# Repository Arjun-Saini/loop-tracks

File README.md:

# loop-tracks

This is the main repository for the loop-tracks project.
The server and UI for this project can be found at [loop-tracks-server](https://github.com/cogsandsquigs/loop-tracks-server) and [loop-tracks-ui](https://github.com/cogsandsquigs/loop-tracks-ui). Full documentation and other information for the project located [here](https://arjun-saini.notion.site/arjun-saini/Loop-Tracks-0d7150e50bd84f2c9db64b674ca986d8).

## images and diagrams

Images and diagrams used in the notion page.

## PCB Design

PCB project files for each track component, designed with [KiCad 6](https://www.kicad.org/).

## master

Master I2C device, code written for a [Particle Argon](https://docs.particle.io/argon/) using DeviceOS 5.0.0.

## slave

Slave I2C devices, code written for an [ATmega328p](https://www.microchip.com/en-us/product/ATmega328).

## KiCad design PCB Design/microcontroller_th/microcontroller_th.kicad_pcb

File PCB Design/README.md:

# loop-tracks PCB designs
These are the PCB designs for the loop-tracks project

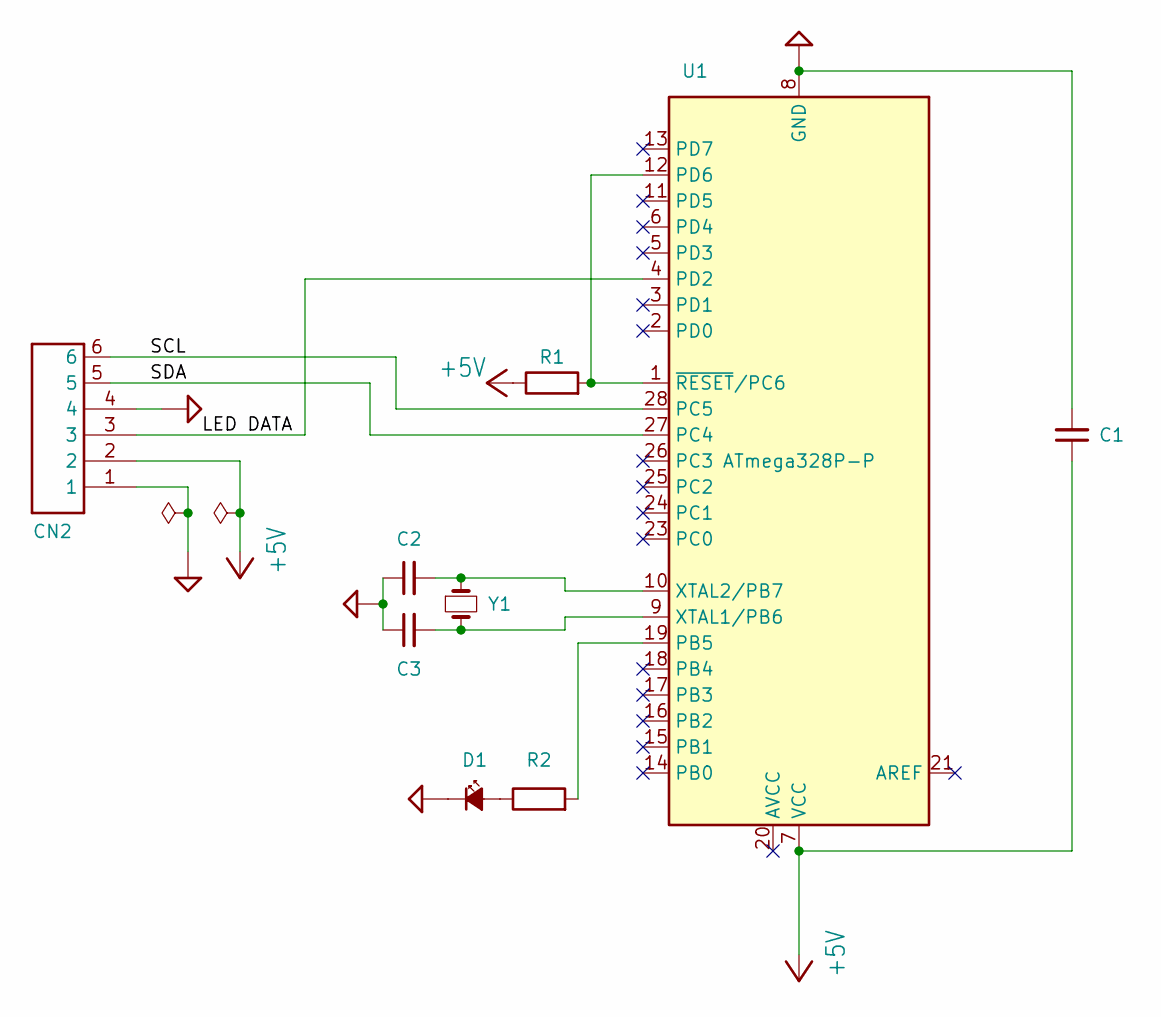
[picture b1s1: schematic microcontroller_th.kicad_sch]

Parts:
C1, C2, C3: C_Small; C_Disc_D4.7mm_W2.5mm_P5.00mm
CN2: 1X4SMT; 1X4-SMT
D1: LED_Small_Filled; LED_D3.0mm
R1, R2: R; R_Axial_DIN0207_L6.3mm_D2.5mm_P7.62mm_Horizontal
U1: ATmega328P-P; DIP-28_W7.62mm
Y1: Crystal_Small; Crystal_HC49-U_Vertical

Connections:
+5V: C1.1, CN2.2, R1.1, U1.7 (VCC)
/LED DATA: CN2.3, U1.4 (PD2)
/SCL: CN2.6, U1.28 (PC5)
/SDA: CN2.5, U1.27 (PC4)
GND: C1.2, C2.1, C3.1, CN2.1, CN2.4, D1.1 (K), U1.8 (GND), U1.22 (GND)
unnamed: C2.2, U1.10 (XTAL2/PB7), Y1.1
unnamed: C3.2, U1.9 (XTAL1/PB6), Y1.2
unnamed: D1.2 (A), R2.1
unnamed: R2.2, U1.19 (PB5)
unnamed: R1.2, U1.1 (~RESET/PC6), U1.12 (PD6)

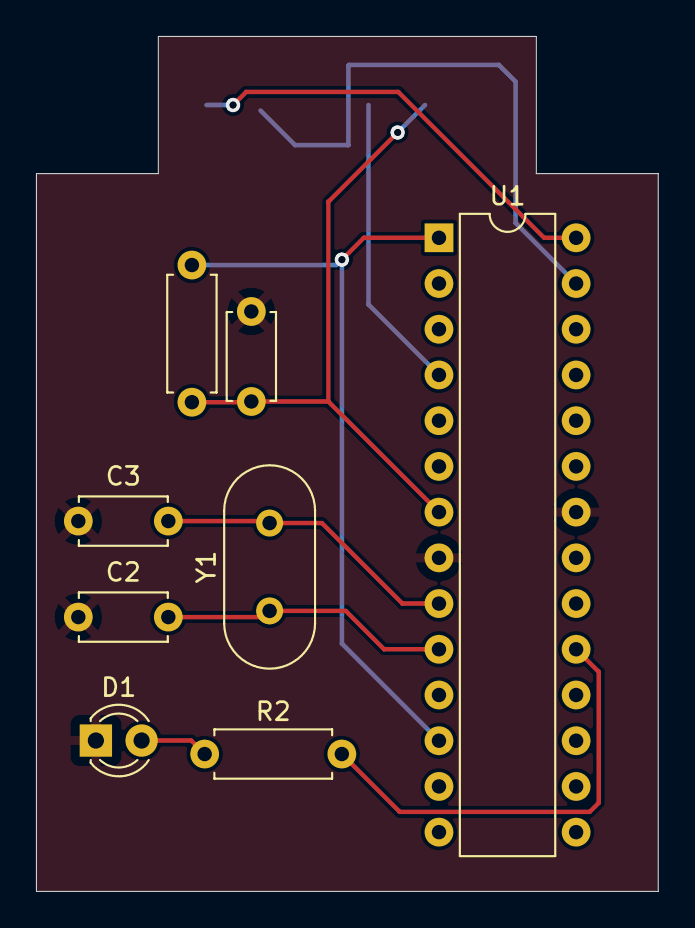
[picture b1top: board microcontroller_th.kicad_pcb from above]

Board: 2 copper layers, 34.5 x 47.5 mm, 9 parts (1 on the bottom side), 10 nets.

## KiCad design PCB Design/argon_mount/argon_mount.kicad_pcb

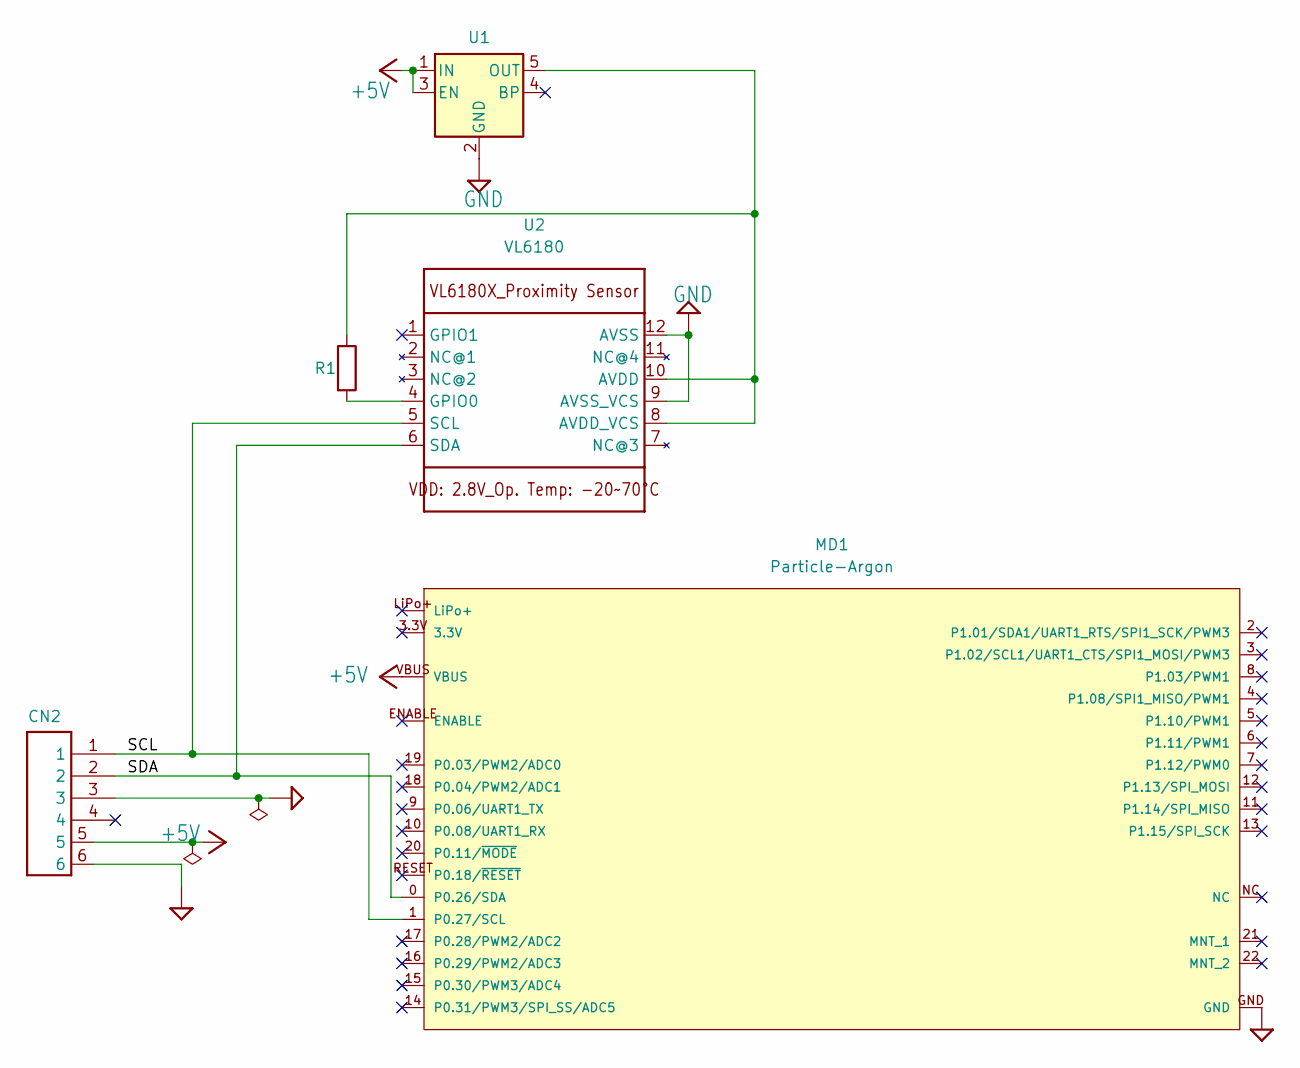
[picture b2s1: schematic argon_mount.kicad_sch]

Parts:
CN2: 1X4SMT; 1X4-SMT
MD1: Particle-Argon; Particle-Argon-0-0-MD1; manufacturer Particle; digikey description Bluetooth, WiFi 802.11b/g/n, Bluetooth 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
R1: R; R_Axial_DIN0207_L6.3mm_D2.5mm_P7.62mm_Horizontal
U1: MIC5219-2.85YM5; SOT-23-5
U2: VL6180

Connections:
+5V: CN2.5, MD1.VBUS, U1.1 (IN), U1.3 (EN)
/SCL: CN2.1, MD1.1 (P0.27/SCL), U2.5 (SCL)
/SDA: CN2.2, MD1.0 (P0.26/SDA), U2.6 (SDA)
GND: CN2.3, CN2.6, MD1.GND, U1.2 (GND), U2.9 (AVSS_VCS), U2.12 (AVSS)
unnamed: R1.1, U1.5 (OUT), U2.8 (AVDD_VCS), U2.10 (AVDD)
unnamed: R1.2, U2.4 (GPIO0)

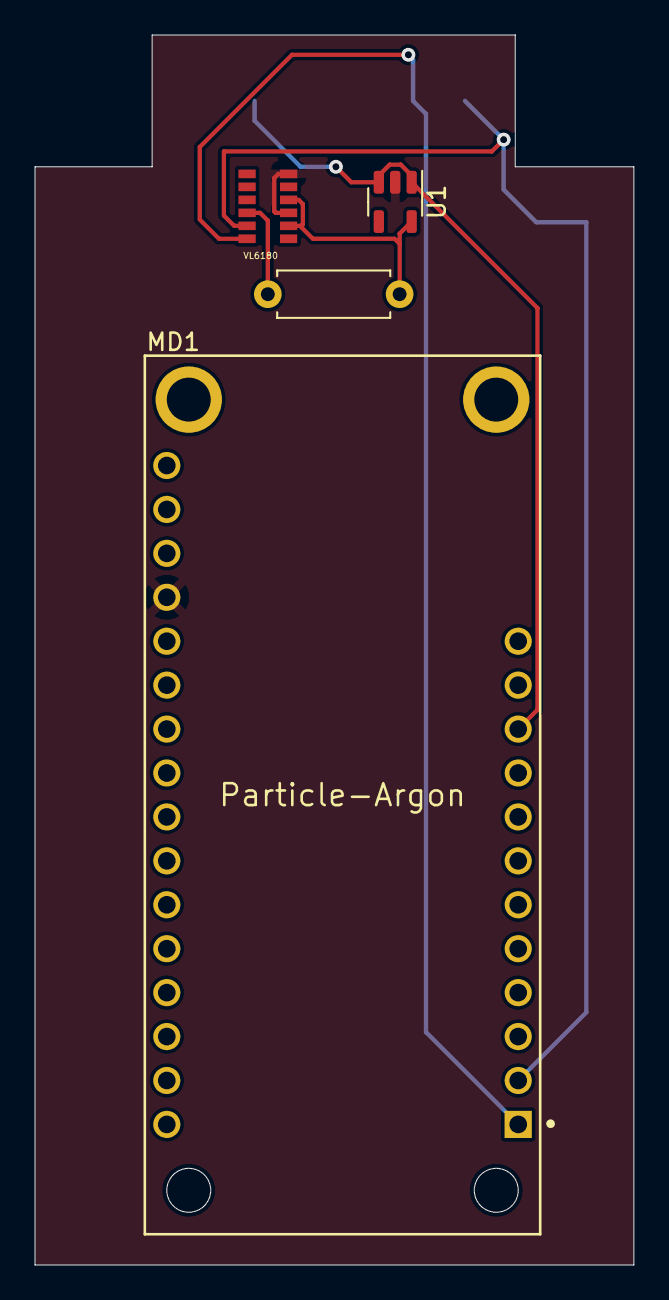
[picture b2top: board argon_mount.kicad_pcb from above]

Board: 2 copper layers, 34.6 x 71.1 mm, 5 parts (1 on the bottom side), 6 nets.

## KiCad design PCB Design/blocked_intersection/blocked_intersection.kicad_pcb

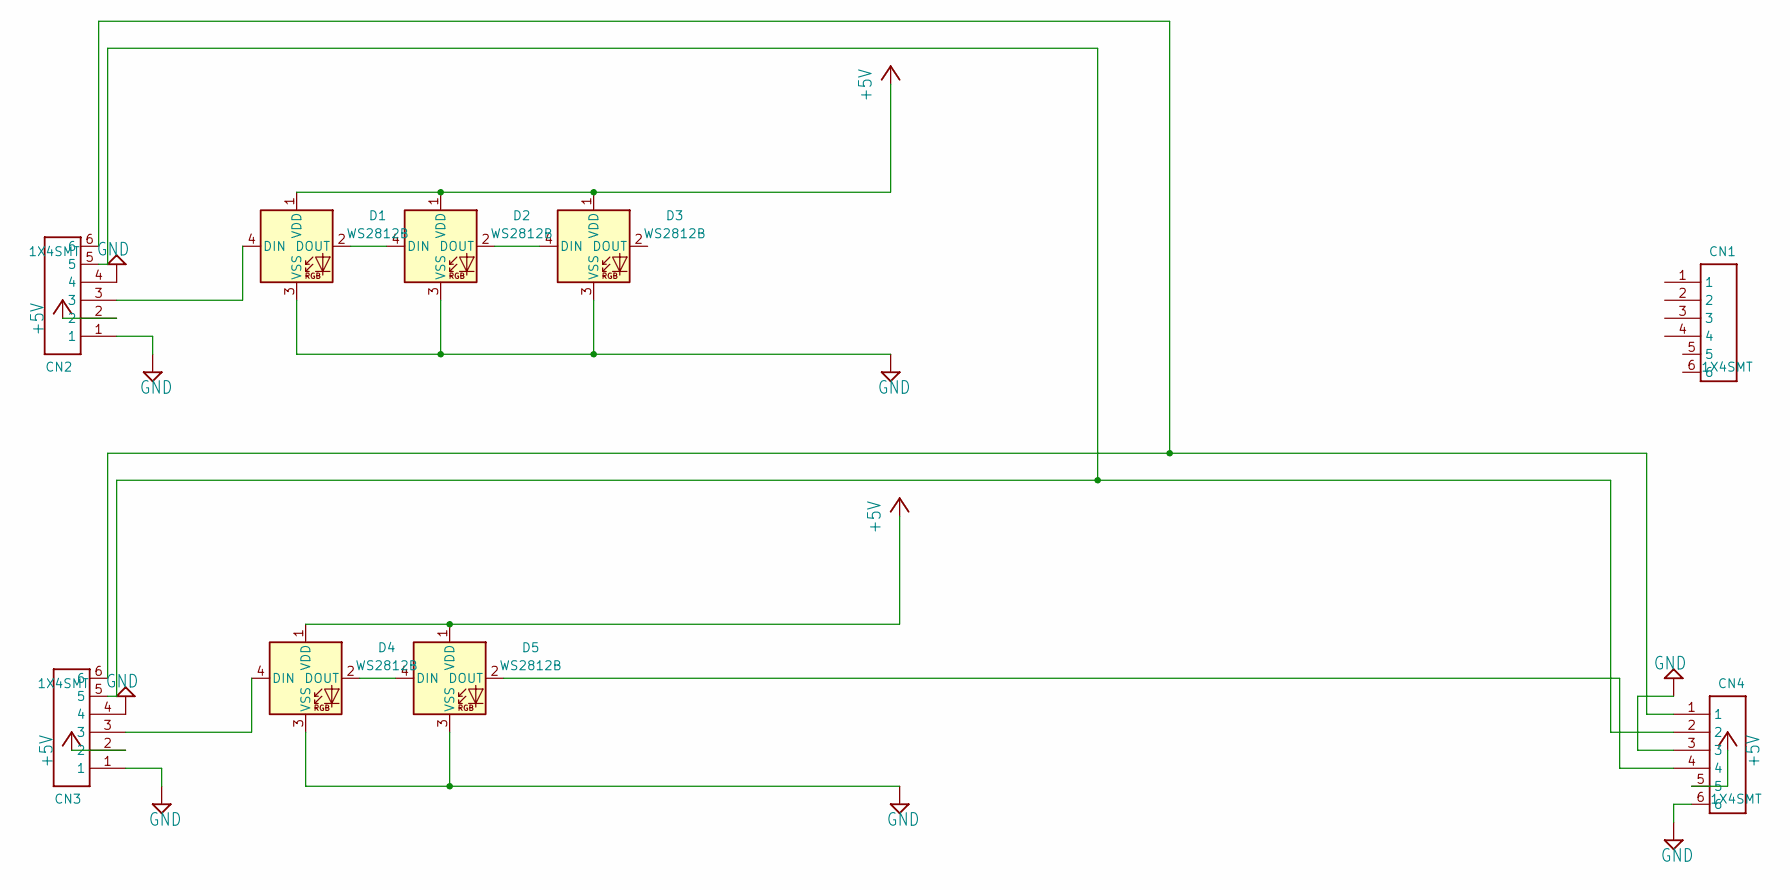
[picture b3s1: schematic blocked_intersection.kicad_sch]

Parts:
CN1, CN2, CN3, CN4: 1X4SMT; 1X4-SMT
D1, D2, D3, D4, D5: WS2812B; LED_WS2812B_PLCC4_5.0x5.0mm_P3.2mm

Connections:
+5V: CN2.2, CN3.2, CN4.5, D1.1 (VDD), D2.1 (VDD), D3.1 (VDD), D4.1 (VDD), D5.1 (VDD)
GND: CN2.1, CN2.4, CN3.1, CN3.4, CN4.3, CN4.6, D1.3 (VSS), D2.3 (VSS), D3.3 (VSS), D4.3 (VSS), D5.3 (VSS)
unnamed: CN2.3, D1.4 (DIN)
unnamed: CN2.5, CN3.5, CN4.2
unnamed: CN2.6, CN3.6, CN4.1
unnamed: CN3.3, D4.4 (DIN)
unnamed: D1.2 (DOUT), D2.4 (DIN)
unnamed: D2.2 (DOUT), D3.4 (DIN)
unnamed: D4.2 (DOUT), D5.4 (DIN)
unnamed: CN4.4, D5.2 (DOUT)

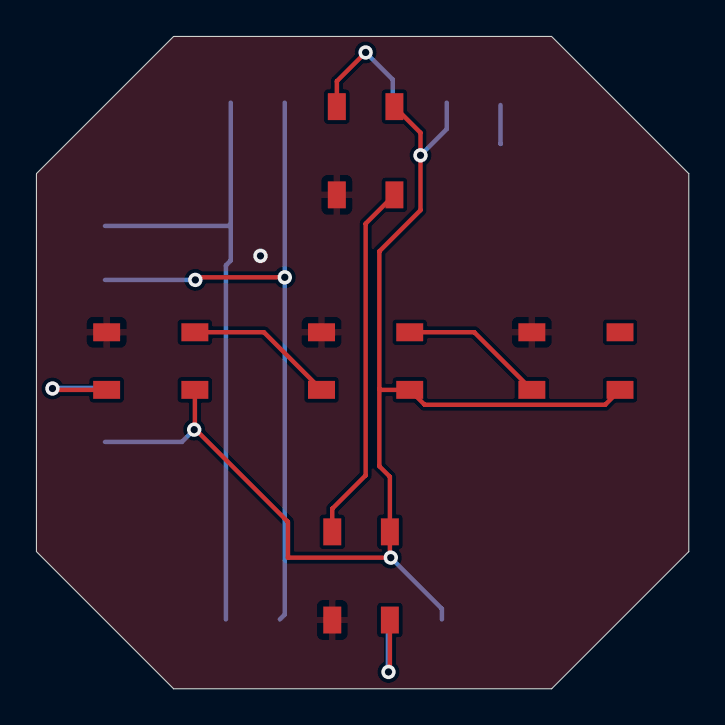
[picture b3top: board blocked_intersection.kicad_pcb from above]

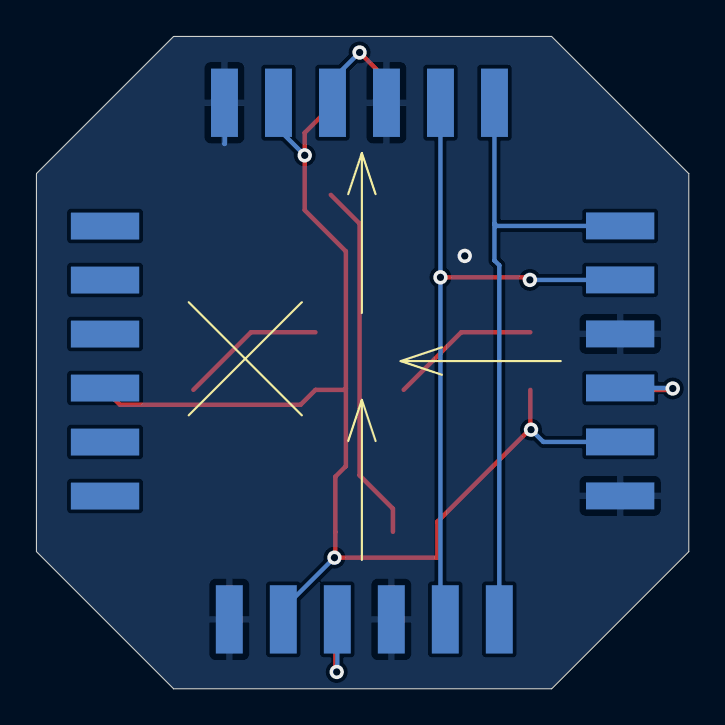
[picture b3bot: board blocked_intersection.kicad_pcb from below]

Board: 2 copper layers, 36.2 x 36.2 mm, 9 parts (4 on the bottom side), 10 nets.

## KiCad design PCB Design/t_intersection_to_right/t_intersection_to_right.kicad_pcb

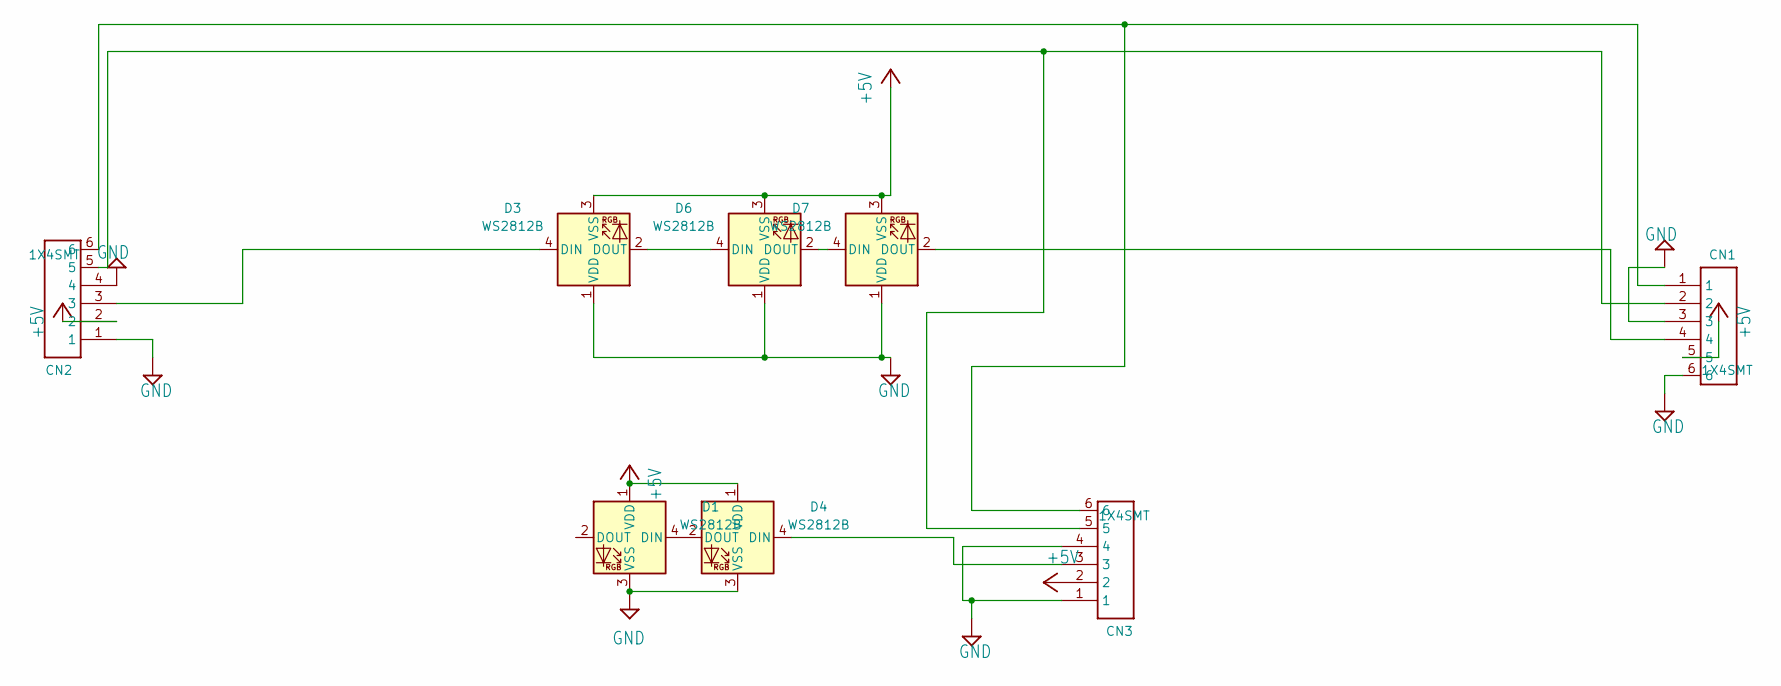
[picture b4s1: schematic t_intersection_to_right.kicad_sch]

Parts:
CN1, CN2, CN3: 1X4SMT; 1X4-SMT
D1, D3, D4, D6, D7: WS2812B; LED_WS2812B_PLCC4_5.0x5.0mm_P3.2mm

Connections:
+5V: CN1.5, CN2.2, CN3.2, D1.1 (VDD), D3.3 (VSS), D4.1 (VDD), D6.3 (VSS), D7.3 (VSS)
GND: CN1.3, CN1.6, CN2.1, CN2.4, CN3.1, CN3.4, D1.3 (VSS), D3.1 (VDD), D4.3 (VSS), D6.1 (VDD), D7.1 (VDD)
unnamed: CN1.1, CN2.6, CN3.6
unnamed: CN1.2, CN2.5, CN3.5
unnamed: CN1.4, D7.2 (DOUT)
unnamed: CN2.3, D3.4 (DIN)
unnamed: CN3.3, D4.4 (DIN)
unnamed: D1.4 (DIN), D4.2 (DOUT)
unnamed: D3.2 (DOUT), D6.4 (DIN)
unnamed: D6.2 (DOUT), D7.4 (DIN)

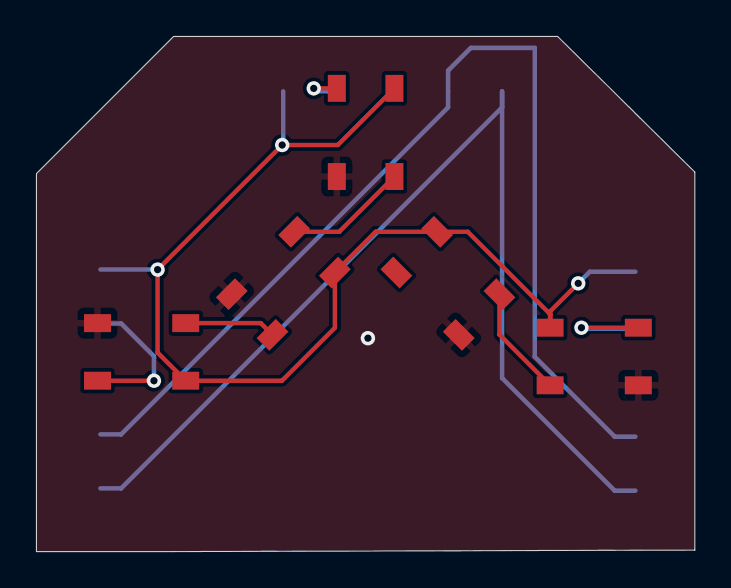
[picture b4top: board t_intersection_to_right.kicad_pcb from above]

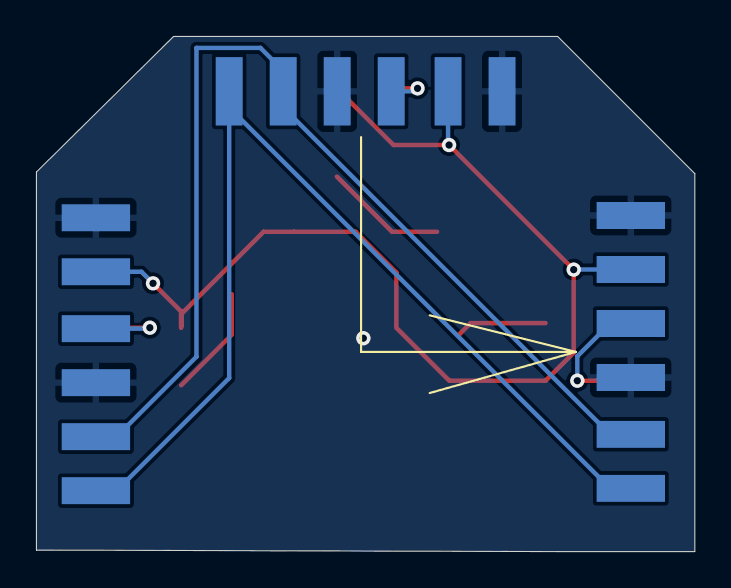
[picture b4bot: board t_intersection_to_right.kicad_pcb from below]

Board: 2 copper layers, 36.6 x 28.6 mm, 8 parts (3 on the bottom side), 10 nets.

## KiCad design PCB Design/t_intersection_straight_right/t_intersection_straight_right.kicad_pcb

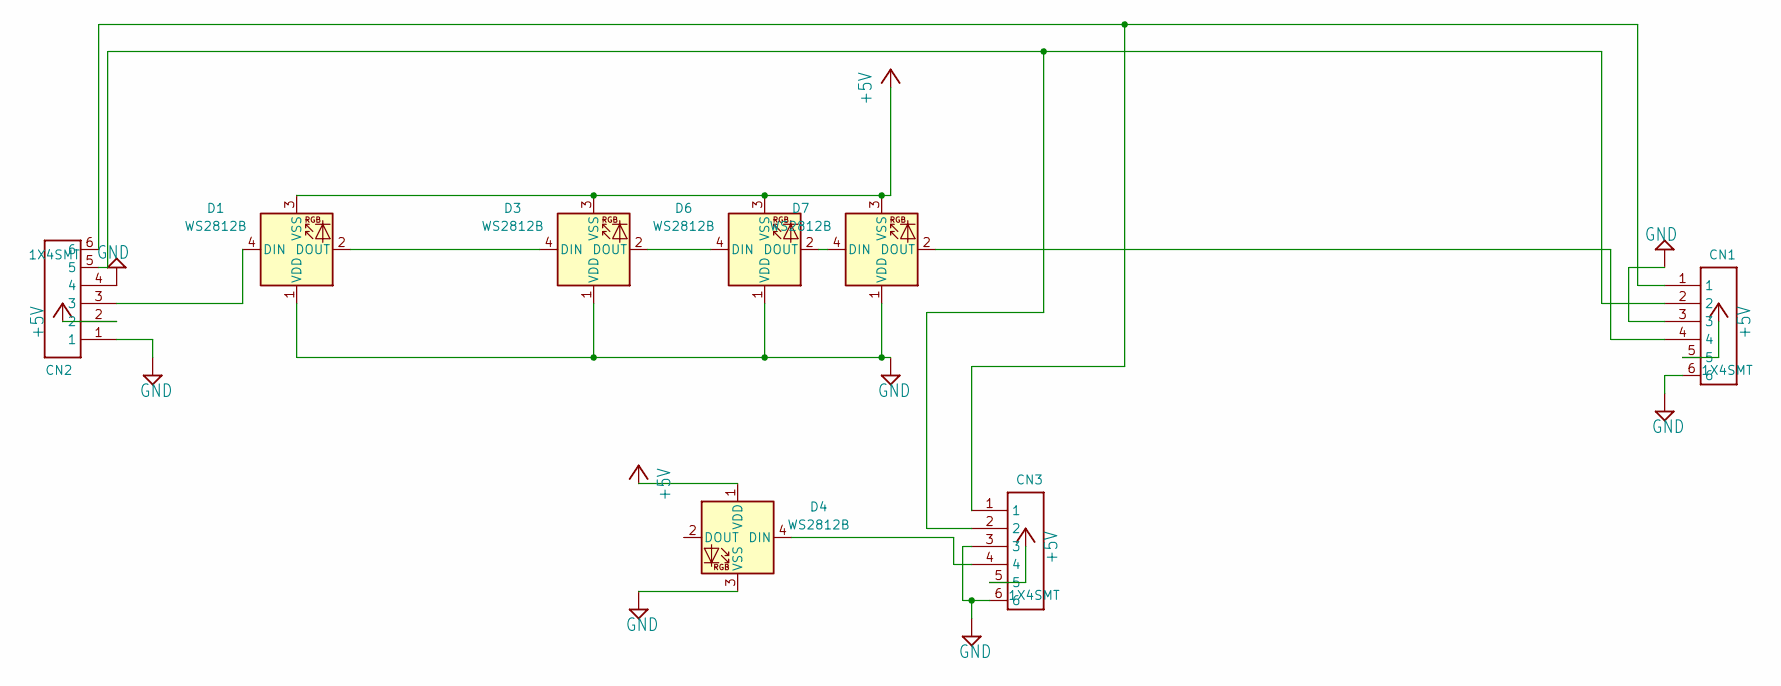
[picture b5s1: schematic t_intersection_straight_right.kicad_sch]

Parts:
CN1, CN2, CN3: 1X4SMT; 1X4-SMT
D1, D3, D4, D6, D7: WS2812B; LED_WS2812B_PLCC4_5.0x5.0mm_P3.2mm

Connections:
+5V: CN1.5, CN2.2, CN3.5, D1.3 (VSS), D3.3 (VSS), D4.1 (VDD), D6.3 (VSS), D7.3 (VSS)
GND: CN1.3, CN1.6, CN2.1, CN2.4, CN3.3, CN3.6, D1.1 (VDD), D3.1 (VDD), D4.3 (VSS), D6.1 (VDD), D7.1 (VDD)
unnamed: CN1.1, CN2.6, CN3.1
unnamed: CN1.2, CN2.5, CN3.2
unnamed: CN1.4, D7.2 (DOUT)
unnamed: CN2.3, D1.4 (DIN)
unnamed: D1.2 (DOUT), D3.4 (DIN)
unnamed: D3.2 (DOUT), D6.4 (DIN)
unnamed: CN3.4, D4.4 (DIN)
unnamed: D6.2 (DOUT), D7.4 (DIN)

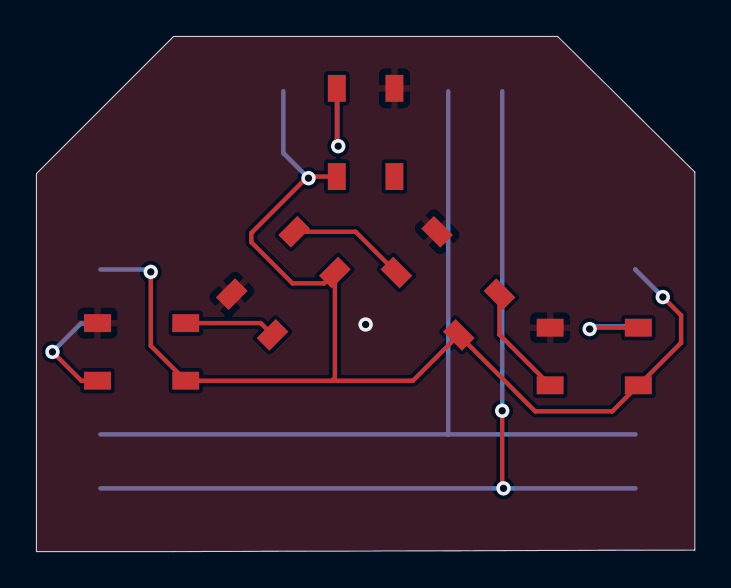
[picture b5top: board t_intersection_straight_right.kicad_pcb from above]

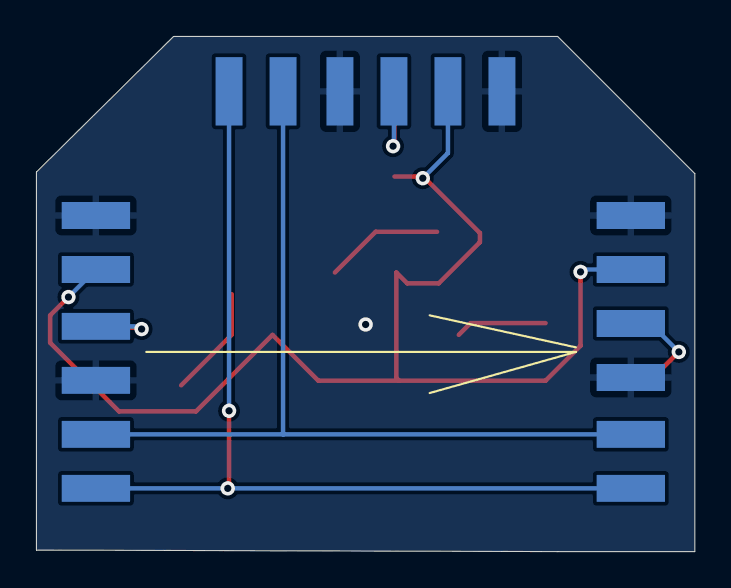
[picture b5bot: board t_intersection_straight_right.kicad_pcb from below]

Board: 2 copper layers, 36.6 x 28.6 mm, 8 parts (3 on the bottom side), 10 nets.

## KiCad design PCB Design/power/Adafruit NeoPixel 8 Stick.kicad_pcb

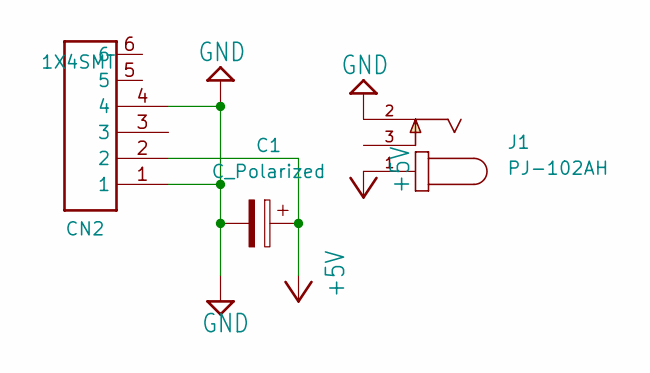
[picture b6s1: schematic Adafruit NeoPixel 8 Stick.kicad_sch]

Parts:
C1: C_Polarized; CP_Radial_D12.5mm_P6.00mm
CN2: 1X4SMT; 1X4-SMT
J1: PJ-102AH

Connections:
+5V: C1.1, CN2.2, J1.1
GND: C1.2, CN2.1, CN2.4, J1.2

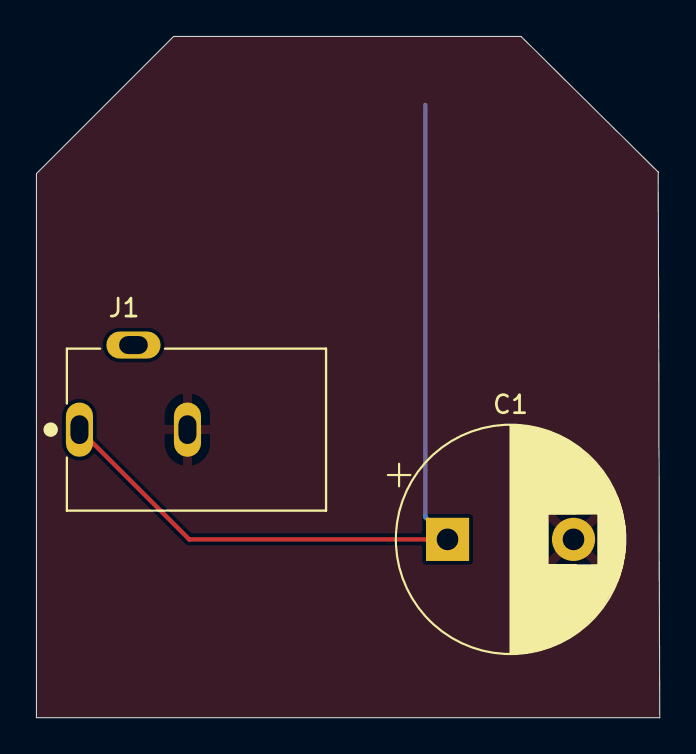
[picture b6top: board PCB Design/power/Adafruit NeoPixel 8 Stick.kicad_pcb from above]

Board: 2 copper layers, 34.6 x 37.8 mm, 3 parts (1 on the bottom side), 2 nets.

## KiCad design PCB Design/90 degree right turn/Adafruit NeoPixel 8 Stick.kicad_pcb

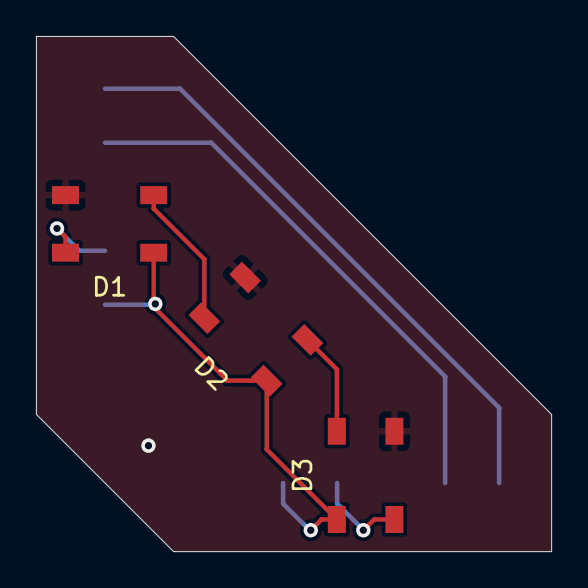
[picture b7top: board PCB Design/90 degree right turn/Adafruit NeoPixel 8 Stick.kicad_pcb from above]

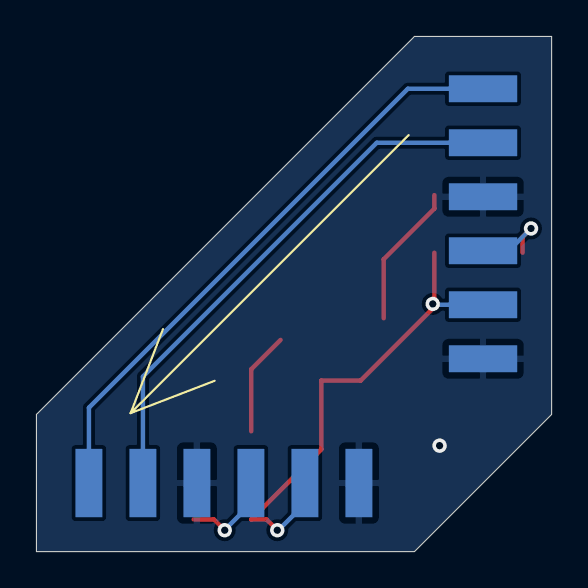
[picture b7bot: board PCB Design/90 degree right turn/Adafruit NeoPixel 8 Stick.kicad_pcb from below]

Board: 2 copper layers, 28.6 x 28.6 mm, 5 parts (2 on the bottom side), 8 nets.

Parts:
CN1, CN2: 1X4SMT; 1X4-SMT
D1, D2, D3: WS2812B; LED_WS2812B_PLCC4_5.0x5.0mm_P3.2mm

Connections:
+5V: CN1.5, CN2.2, D1.1 (VDD), D2.1 (VDD), D3.1 (VDD)
GND: CN1.3, CN1.6, CN2.1, CN2.4, D1.3 (VSS), D2.3 (VSS), D3.3 (VSS)
unnamed: CN1.1, CN2.6
unnamed: CN1.2, CN2.5
unnamed: CN2.3, D1.4 (DIN)
unnamed: D1.2 (DOUT), D2.4 (DIN)
unnamed: D2.2 (DOUT), D3.4 (DIN)
unnamed: CN1.4, D3.2 (DOUT)

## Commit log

2021-07-22 new project
2021-07-27 scanning algorithm
2021-07-27 i2c address algorithm
2021-07-28 ble sequence
2021-08-04 train position using prediction
2021-08-17 red line dotstar
2021-08-17 one slave display
2021-08-19 blue line data
2022-06-28 nearest checkpoint
2022-06-28 red line neopixel
2022-06-28 railway vectors
2022-06-29 multi line colors
2022-06-29 linked list
2022-06-30 loop
2022-06-30 fix end loop
2022-07-01 crash fix
2022-07-01 three lines
2022-07-01 orange fix
2022-07-05 cta api
2022-07-05 end pixel fix
2022-07-06 straight stick
2022-07-06 cleaner routing
2022-07-06 4 pin fix
2022-07-06 90 connectors
2022-07-06 45 connector
2022-07-06 4 way intersection
2022-07-06 arrows
2022-07-07 6 pin
2022-07-08 track split
2022-07-08 split fix
2022-07-08 green split
2022-07-08 blue line fix
2022-07-08 single loop
2022-07-08 loop lines separate
2022-07-11 single loop line
2022-07-11 brown/purple merge
2022-07-11 5 line test
2022-07-11 green
2022-07-11 added beginnings of t junction
2022-07-12 changes to T intersection
2022-07-12 green merge
2022-07-12 made microcontroller mount
2022-07-12 added argon mount
2022-07-12 brown line flip
2022-07-12 orange pos
2022-07-12 finished power supply
2022-07-12 left t junction update
2022-07-12 slave update
2022-07-12 added straight t intersection
2022-07-12 added README
2022-07-12 purple fix
2022-07-12 added another readme
2022-07-13 basic ble setup
2022-07-13 green ble fix
2022-07-13 comments
2022-07-13 cities
2022-07-13 cities update
2022-07-13 ble updates
2022-07-13 ble ui
2022-07-14 mbta
2022-07-14 slave blink
2022-07-14 ble crash fix
2022-07-14 mbta direction fix
2022-07-14 uuid
2022-07-14 green merge fix
2022-07-15 i2c randomize fix
2022-07-15 t intersections
2022-07-15 half size straight stick
2022-07-18 mount edges
2022-07-18 proximity sensor
2022-07-18 mqtt
2022-07-18 arduino slave
2022-07-19 compartmentalized parsing code
2022-07-20 porting to arduino
2022-07-20 init my own dir
2022-07-20 added hex stuffs
2022-07-20 arduino port
2022-07-20 mqtt loop
2022-07-20 proximity fix
2022-07-20 parse train
2022-07-20 device id
2022-07-21 randomize efficiency
2022-07-21 t straight fix
2022-07-21 argon mount
2022-07-21 cleanup
2022-07-22 segment display pcb
2022-07-22 display
2022-07-22 redo microcontroller board
2022-07-27 aughe
2022-07-28 rm master warnings
2022-07-28 ok things working??
2022-07-28 auge
2022-07-28 yaay it works
2022-07-28 changed pcbs
2022-07-28 changes changes
2022-07-28 strip.show runs all the time now
2022-07-28 yay other stuff workes
2022-07-28 change update var to refresh
2022-07-28 edited boards
2022-08-03 yarg
2022-08-05 updated some pcbs
2022-08-05 clean up boards + generate some gerber files
2022-08-08 rm vias over pads
2022-08-08 move vias off pads
2022-08-08 arduino reboot
2022-08-08 renamed project files
2022-08-09 twiboot
2022-08-09 eeprom address
2022-08-09 update timer
2022-08-09 atmega reset
2022-08-09 Squashed commit of the following:
    commit 3b9e75c34fcf5fbcdf9d23706f6c16b9b6f41cae
    Author: Arjun-Saini <69866165+Arjun-Saini@users.noreply.github.com>
    Date: Tue Aug 9 10:25:40 2022 -0500
    atmega reset
2022-08-09 twiboot update
2022-08-09 flash multiple
2022-08-10 default i2c address
2022-08-10 Squashed commit of the following:
    commit fec475bc2439b68e55e24e4c5f1c8fdf8befaca8
    Author: Arjun-Saini <69866165+Arjun-Saini@users.noreply.github.com>
    Date: Wed Aug 10 10:48:40 2022 -0500
    updates
    commit a9c843ba1130c47e679f72f1772a47571245f3ed
    Merge: c6533b8 d890383
2022-08-11 sensor 0x30
2022-08-11 multithreading
2022-08-11 thread fix
2022-08-15 cloud
2022-08-15 format
2022-08-16 brown flicker fix
2022-08-16 argon pcb fix
2022-08-17 system block update
2022-08-17 t-intersection pcbs
2022-08-18 power pcb fix
2022-08-18 organization
2022-08-18 added gitignore
2022-08-19 blocked intersection
2022-08-22 clean algorithm
2022-08-22 lightshow power reduction
2022-08-22 repo cleanup
2022-08-23 readme
2022-08-24 mount fix + offshoot flip
2022-08-25 displays
2022-08-26 images
